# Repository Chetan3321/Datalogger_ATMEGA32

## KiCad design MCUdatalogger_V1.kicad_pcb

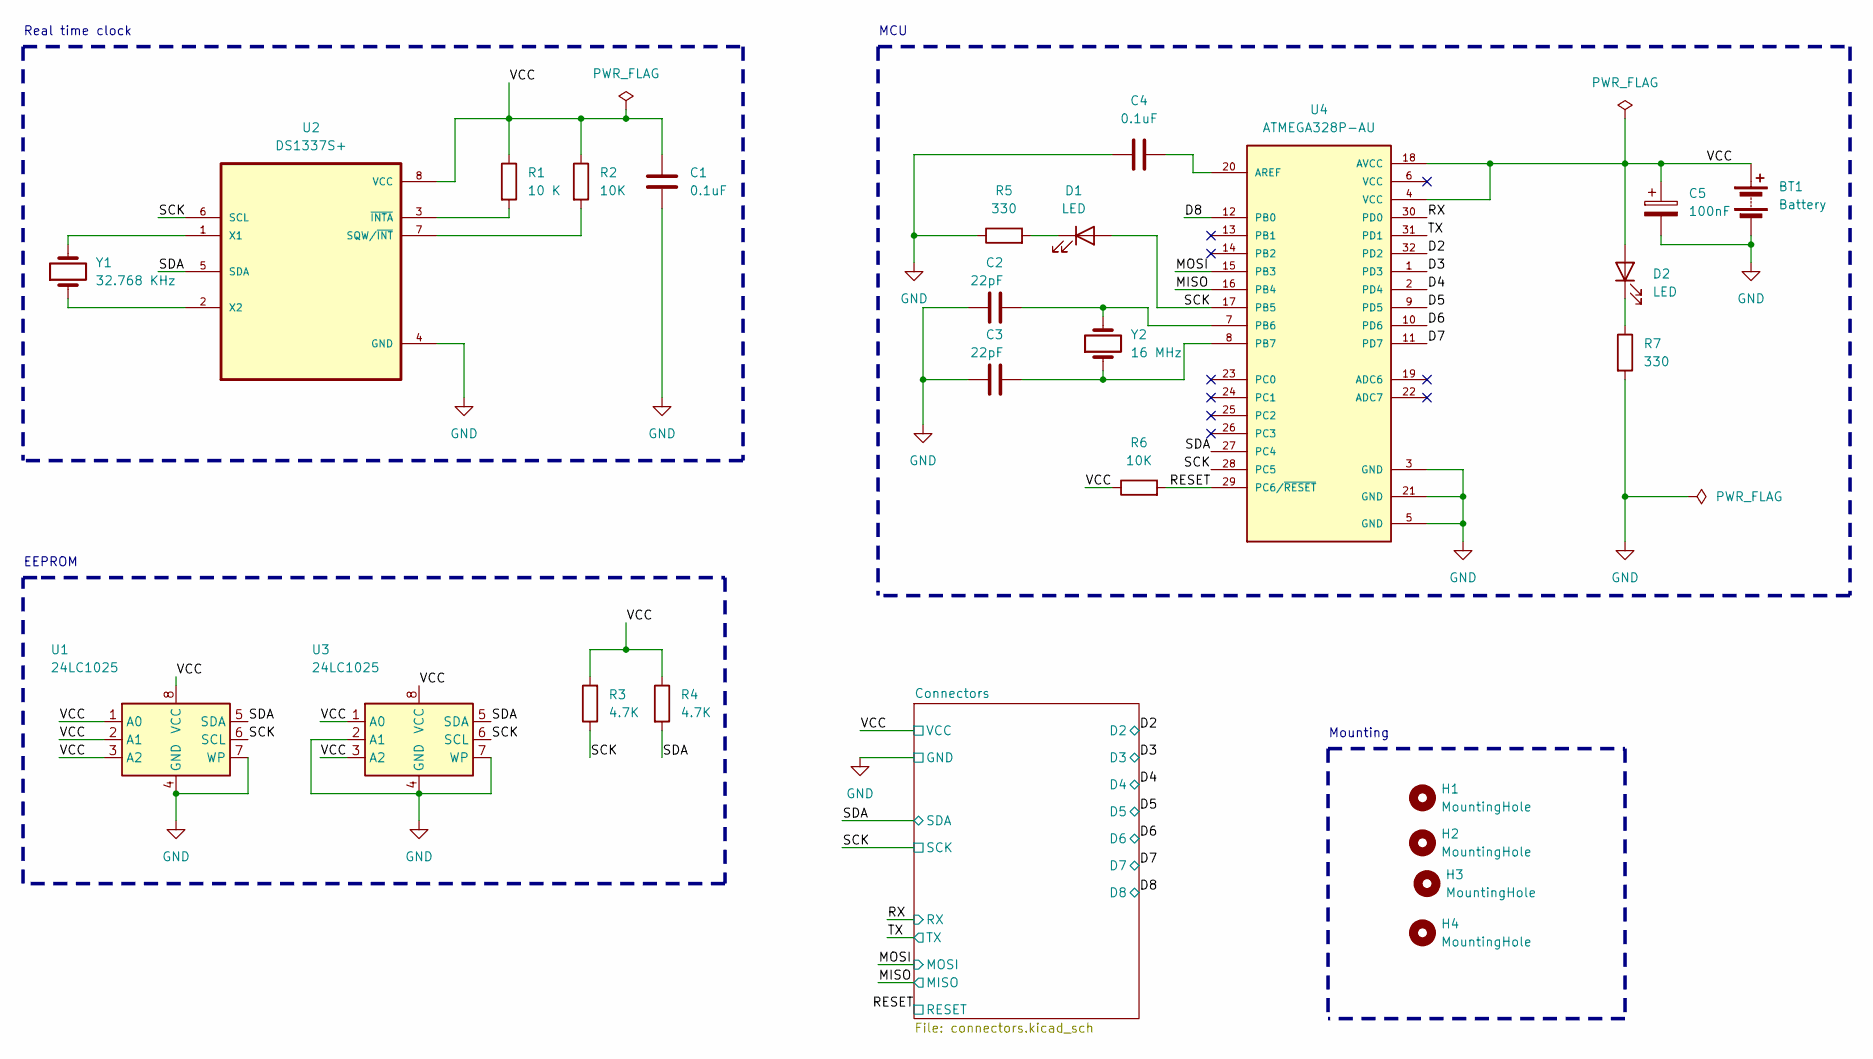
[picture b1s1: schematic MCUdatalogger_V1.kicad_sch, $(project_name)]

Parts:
BT1: Battery; PinHeader_1x02_P2.54mm_Vertical
C1, C4: 0.1uF; C_0805_2012Metric
C2, C3: 22pF; C_0805_2012Metric
C5: 100nF; C_0805_2012Metric
D1, D2: LED; LED_0805_2012Metric
H1, H2, H3, H4: MountingHole; MountingHole_2.1mm
R1: 10 K; R_0805_2012Metric
R2, R6: 10K; R_0805_2012Metric
R3, R4: 4.7K; R_0805_2012Metric
R5, R7: 330; R_0805_2012Metric
U1, U3: 24LC1025; SOIC-8_5.23x5.23mm_P1.27mm
U2: DS1337S+; SOIC127P600X175-8N
U4: ATMEGA328P-AU; QFP80P900X900X120-32N; PARTREV 8271A
Y1: 32.768 KHz; Crystal_SMD_5032-2Pin_5.0x3.2mm_HandSoldering
Y2: 16 MHz; Crystal_SMD_5032-2Pin_5.0x3.2mm_HandSoldering

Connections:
/D2: U4.32 (PD2); also elsewhere on the board
/D3: U4.1 (PD3); also elsewhere on the board
/D4: U4.2 (PD4); also elsewhere on the board
/D5: U4.9 (PD5); also elsewhere on the board
/D6: U4.10 (PD6); also elsewhere on the board
/D7: U4.11 (PD7); also elsewhere on the board
/D8: U4.12 (PB0); also elsewhere on the board
/MISO: U4.16 (PB4); also elsewhere on the board
/MOSI: U4.15 (PB3); also elsewhere on the board
/RESET: R6.2, U4.29 (PC6/~RESET); also elsewhere on the board
/RX: U4.30 (PD0); also elsewhere on the board
/SCK: D1.2 (A), R3.1, U1.6 (SCL), U2.6 (SCL), U3.6 (SCL), U4.17 (PB5), U4.28 (PC5); also elsewhere on the board
/SDA: R4.2, U1.5 (SDA), U2.5 (SDA), U3.5 (SDA), U4.27 (PC4); also elsewhere on the board
/TX: U4.31 (PD1); also elsewhere on the board
/VCC: BT1.1 (+), C1.1, C5.1, D2.2 (A), R1.1, R2.1, R3.2, R4.1, R6.1, U1.1 (A0), U1.2 (A1), U1.3 (A2), U1.8 (VCC), U2.8 (VCC), U3.1 (A0), U3.3 (A2), U3.8 (VCC), U4.4 (VCC), U4.18 (AVCC); also elsewhere on the board
GND: BT1.2 (-), C1.2, C2.1, C3.1, C4.1, C5.2, R5.1, R7.2, U1.4 (GND), U1.7 (WP), U2.4 (GND), U3.2 (A1), U3.4 (GND), U3.7 (WP), U4.3 (GND), U4.5 (GND), U4.21 (GND); also elsewhere on the board
unnamed: D1.1 (K), R5.2
unnamed: D2.1 (K), R7.1
unnamed: R2.2, U2.7 (SQW/~INT)
unnamed: U2.1 (X1), Y1.2
unnamed: U2.2 (X2), Y1.1
unnamed: R1.2, U2.3 (~INTA)
unnamed: C4.2, U4.20 (AREF)
unnamed: C2.2, U4.7 (PB6), Y2.2
unnamed: C3.2, U4.8 (PB7), Y2.1

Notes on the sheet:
MCU
Real time clock
Mounting
EEPROM

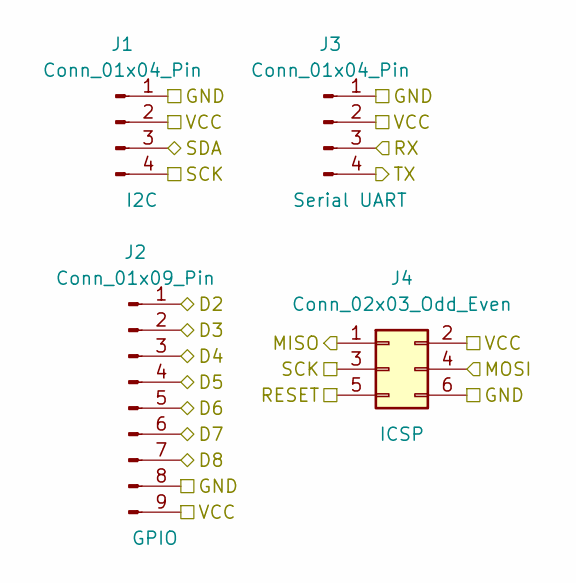
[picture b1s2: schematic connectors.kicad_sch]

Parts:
J1, J3: Conn_01x04_Pin; PinHeader_1x04_P2.54mm_Vertical
J2: Conn_01x09_Pin; PinHeader_1x09_P2.54mm_Vertical
J4: Conn_02x03_Odd_Even; PinHeader_2x03_P2.54mm_Vertical

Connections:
/D2: J2.1; also elsewhere on the board
/D3: J2.2; also elsewhere on the board
/D4: J2.3; also elsewhere on the board
/D5: J2.4; also elsewhere on the board
/D6: J2.5; also elsewhere on the board
/D7: J2.6; also elsewhere on the board
/D8: J2.7; also elsewhere on the board
/MISO: J4.1; also elsewhere on the board
/MOSI: J4.4; also elsewhere on the board
/RESET: J4.5; also elsewhere on the board
/RX: J3.3; also elsewhere on the board
/SCK: J1.4, J4.3; also elsewhere on the board
/SDA: J1.3; also elsewhere on the board
/TX: J3.4; also elsewhere on the board
/VCC: J1.2, J2.9, J3.2, J4.2; also elsewhere on the board
GND: J1.1, J2.8, J3.1, J4.6; also elsewhere on the board

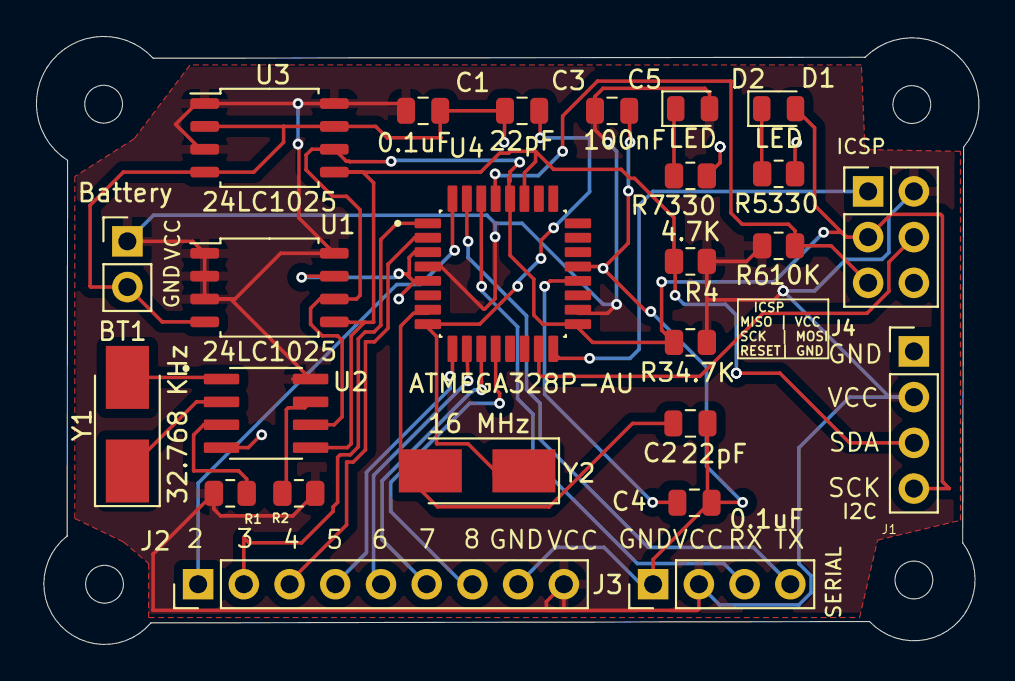
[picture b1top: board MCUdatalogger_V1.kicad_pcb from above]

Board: 2 copper layers, 52.4 x 33.8 mm, 30 parts (1 on the bottom side), 25 nets.

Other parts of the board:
REF: KiCad-Logo2_5mm_SilkScreen

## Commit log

2024-06-28 Initiating the data logger
2024-06-30 Changed location of symbols
2024-06-30 Completed symbol - footprint associations.
2024-06-30 Complete wiring in the second sheet
2024-06-30 Completed comments.
2024-06-30 PCB Started
2024-07-01 Connections established
2024-07-01 PCB Ready
2024-07-02 3D View updated
2024-07-02 Added gerber
